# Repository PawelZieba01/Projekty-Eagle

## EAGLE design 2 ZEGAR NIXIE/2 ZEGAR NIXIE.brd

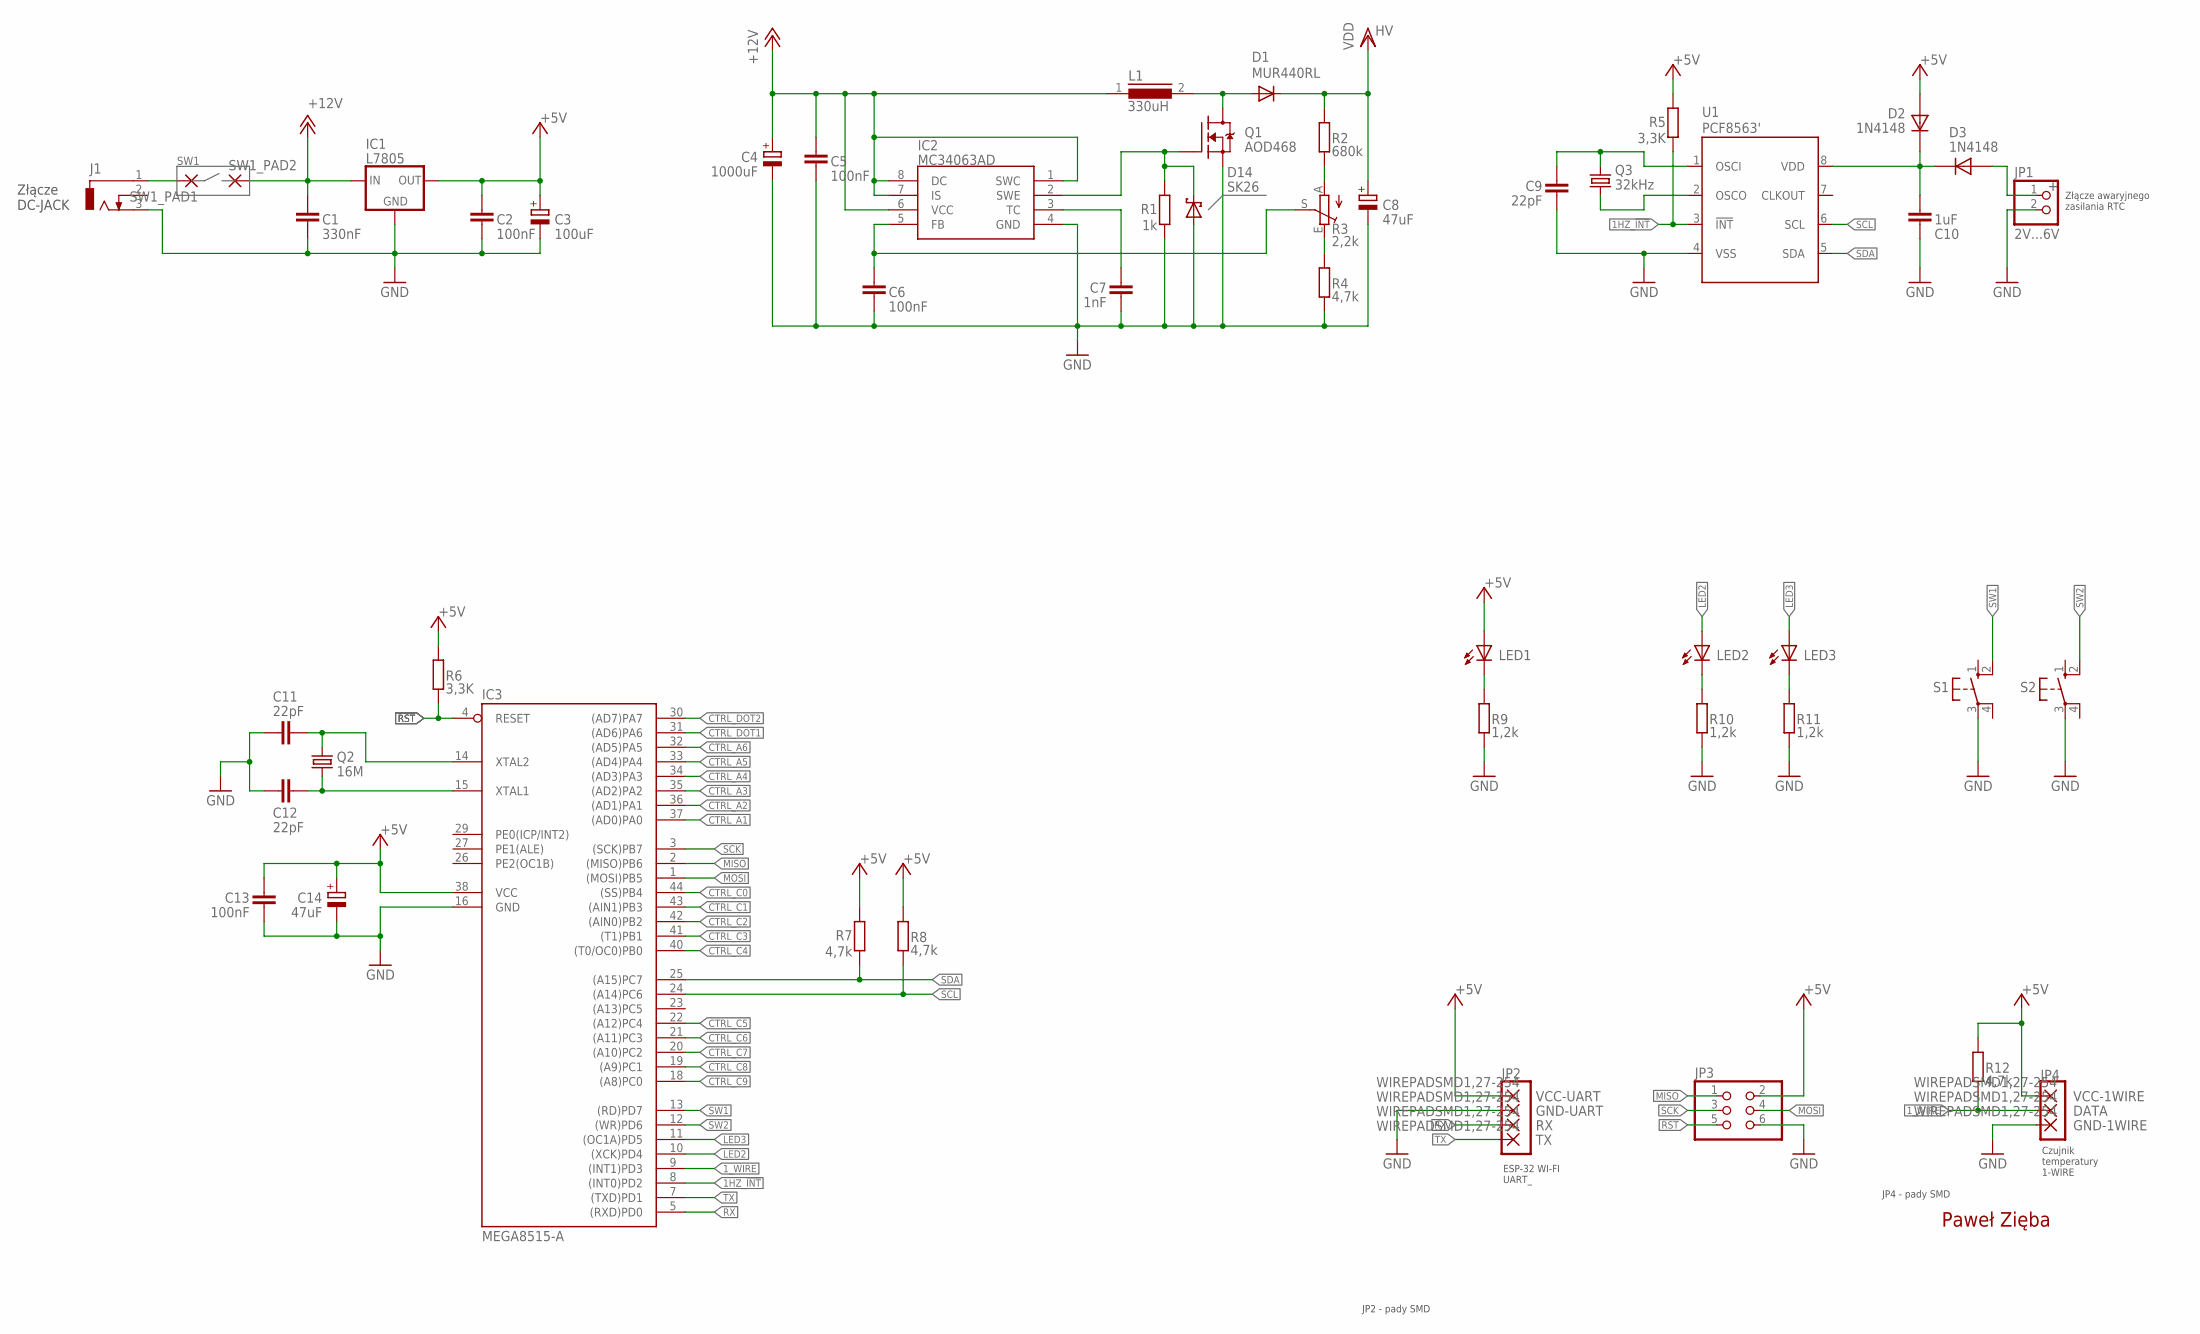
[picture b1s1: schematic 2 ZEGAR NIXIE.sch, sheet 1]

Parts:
C1: 330nF; C1206
C2, C5, C6, C13: 100nF; C1206
C3: 100uF; E5-10,5
C4: 1000uF; E5-10,5
C7: 1nF; C1206
C8: 47uF; E5-13
C9, C11, C12: 22pF; C1206
C10: 1uF; C1206
C14: 47uF; UD-6,3X5,8_NICHICON
D1: MUR440RL; C2673
D2, D3: 1N4148; D1206
D14: SK26; SMB
DATA: WIREPADSMD1,27-254; SMD1,27-2,54
GND-1WIRE: WIREPADSMD1,27-254; SMD1,27-2,54
GND-UART: WIREPADSMD1,27-254; SMD1,27-2,54
IC1: L7805; DPAK
IC2: MC34063AD; SOIC8
IC3: MEGA8515-A; TQFP44
J1: DCJ0303
JP1: 2V...6V; 1X02
JP3: PINHD-2X3; 2X03
L1: 330uH; SFT830D
LED1, LED2, LED3: LED_E; LED_1206
Q1: AOD468; DPAK-TO252
Q2: 16M; 2.5X2.0_KX-6
Q3: 32kHz; TC26H
R1: 1k; R0805
R2: 680k; R0805
R3: 2,2k; CA6V
R4: 4,7k; R0805
R5, R6: 3,3K; R1206
R7, R8, R12: 4,7k; R1206
R9, R10, R11: 1,2k; R1206
RX: WIREPADSMD1,27-254; SMD1,27-2,54
S1, S2: 10-XX; B3F-10XX
SW1_PAD1, SW1_PAD2: 3,81/1,4
TX: WIREPADSMD1,27-254; SMD1,27-2,54
U1: PCF8563'; SO08-IRF
VCC-1WIRE: WIREPADSMD1,27-254; SMD1,27-2,54
VCC-UART: WIREPADSMD1,27-254; SMD1,27-2,54

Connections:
1HZ_!INT: IC3.8 ((INT0)PD2), R5.1, U1.3 (!INT)
1_WIRE: DATA.1, IC3.9 ((INT1)PD3), R12.1
!RST: IC3.4 (RESET), JP3.5, R6.1
+5V: C2.1, C3.+, C13.2, C14.+, D2.1 (+), IC1.3 (OUT), IC3.38 (VCC), JP3.2, LED1.A, R5.2, R6.2, R7.2, R8.2, R12.2, VCC-1WIRE.1, VCC-UART.1
+12V: C1.1, C4.+, C5.1, IC1.1 (IN), IC2.1 (SWC), IC2.6 (VCC), IC2.7 (IS), IC2.8 (DC), L1.1, SW1_PAD2.1
CTRL_A1: IC3.37 ((AD0)PA0); also elsewhere on the board
CTRL_A2: IC3.36 ((AD1)PA1); also elsewhere on the board
CTRL_A3: IC3.35 ((AD2)PA2); also elsewhere on the board
CTRL_A4: IC3.34 ((AD3)PA3); also elsewhere on the board
CTRL_A5: IC3.33 ((AD4)PA4); also elsewhere on the board
CTRL_A6: IC3.32 ((AD5)PA5); also elsewhere on the board
CTRL_C0: IC3.44 ((SS)PB4); also elsewhere on the board
CTRL_C1: IC3.43 ((AIN1)PB3); also elsewhere on the board
CTRL_C2: IC3.42 ((AIN0)PB2); also elsewhere on the board
CTRL_C3: IC3.41 ((T1)PB1); also elsewhere on the board
CTRL_C4: IC3.40 ((T0/OC0)PB0); also elsewhere on the board
CTRL_C5: IC3.22 ((A12)PC4); also elsewhere on the board
CTRL_C6: IC3.21 ((A11)PC3); also elsewhere on the board
CTRL_C7: IC3.20 ((A10)PC2); also elsewhere on the board
CTRL_C8: IC3.19 ((A9)PC1); also elsewhere on the board
CTRL_C9: IC3.18 ((A8)PC0); also elsewhere on the board
CTRL_DOT1: IC3.31 ((AD6)PA6); also elsewhere on the board
CTRL_DOT2: IC3.30 ((AD7)PA7); also elsewhere on the board
GND: C1.2, C2.2, C3.-, C4.-, C5.2, C6.2, C7.2, C8.-, C9.2, C10.2, C11.1, C12.1, C13.1, C14.-, D14.A, GND-1WIRE.1, GND-UART.1, IC1.2 (GND), IC2.4 (GND), IC3.16 (GND), J1.3, JP1.2, JP3.6, Q1.3 (S), R1.1, R4.1, R9.1, R10.1, R11.1, S1.3, S2.3, U1.4 (VSS); also elsewhere on the board
HV: C8.+, D1.C, R2.2; also elsewhere on the board
LED2: IC3.10 ((XCK)PD4), LED2.A
LED3: IC3.11 ((OC1A)PD5), LED3.A
MISO: IC3.2 ((MISO)PB6), JP3.1
MOSI: IC3.1 ((MOSI)PB5), JP3.4
unnamed: J1.1, SW1_PAD1.1
unnamed: R2.1, R3.A
unnamed: C7.1, IC2.3 (TC)
unnamed: R3.E, R4.2
unnamed: C11.2, IC3.14 (XTAL2), Q2.3 (2)
unnamed: D14.C, IC2.2 (SWE), Q1.1 (G), R1.2
unnamed: D1.A, L1.2, Q1.2 (D)
unnamed: C6.1, IC2.5 (FB), R3.S
unnamed: LED1.C, R9.2
unnamed: C12.2, IC3.15 (XTAL1), Q2.1
unnamed: Q3.1, U1.2 (OSCO)
unnamed: C9.1, Q3.2, U1.1 (OSCI)
unnamed: C10.1, D2.2 (-), D3.2 (-), U1.8 (VDD)
unnamed: D3.1 (+), JP1.1
unnamed: LED2.C, R10.2
unnamed: LED3.C, R11.2
RX: IC3.5 ((RXD)PD0), RX.1
SCK: IC3.3 ((SCK)PB7), JP3.3
SCL: IC3.24 ((A14)PC6), R8.1, U1.6 (SCL)
SDA: IC3.25 ((A15)PC7), R7.1, U1.5 (SDA)
SW1: IC3.13 ((RD)PD7), S1.2 (S1)
SW2: IC3.12 ((WR)PD6), S2.2 (S1)
TX: IC3.7 ((TXD)PD1), TX.1

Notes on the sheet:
SW1
Złącze awaryjnego zasilania RTC
Czujnik temperatury 1-WIRE
ESP-32 WI-FI UART_
Paweł Zięba
Złącze DC-JACK
JP2
JP4
JP2 - pady SMD
JP4 - pady SMD

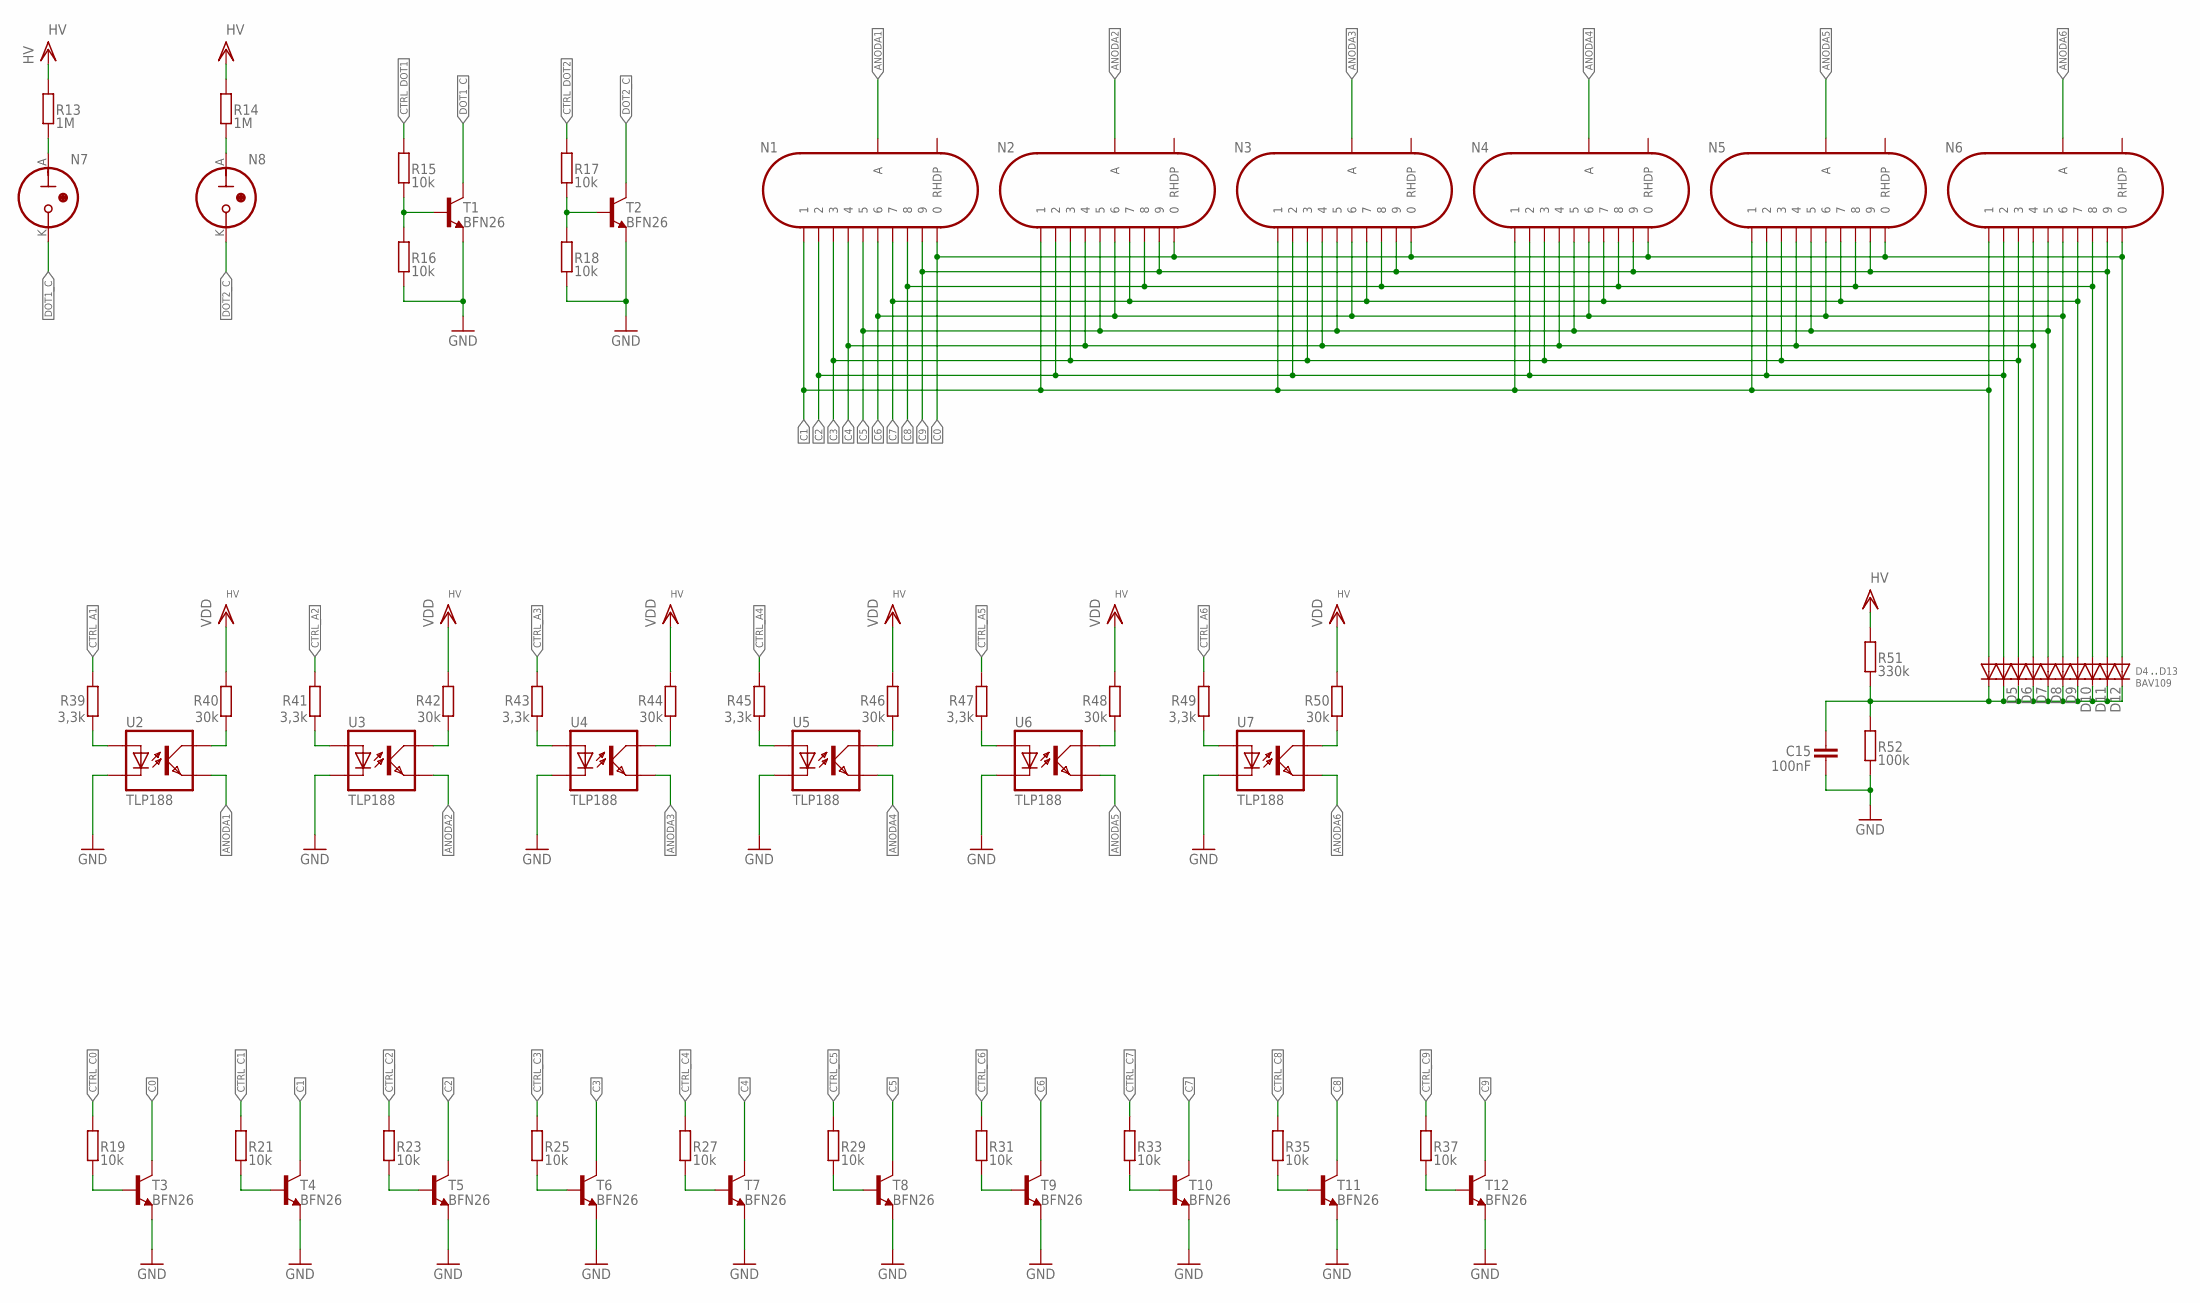
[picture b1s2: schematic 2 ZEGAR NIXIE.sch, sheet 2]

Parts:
C15: 100nF; C1206
D4, D5, D6, D7, D8, D9, D10, D11, D12: DIODE-MINIMELF; MINIMELF
D13: BAV109; MINIMELF
N1, N2, N3, N4, N5, N6: IN-8-2
N7, N8: IN-3
R13, R14: 1M; R1206
R15, R16, R17, R18, R19, R21, R23, R25, R27, R29, R31, R33, R35, R37: 10k; R0805
R39, R41, R43, R45, R47, R49: 3,3k; R0805
R40, R42, R44, R46, R48, R50: 30k; R1206
R51: 330k; R1206
R52: 100k; R1206
T1, T2, T3, T4, T5, T6, T7, T8, T9, T10, T11, T12: BFN26; SOT23-BEC
U2, U3, U4, U5, U6, U7: TLP188; 11-4M1S

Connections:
ANODA1: N1.A, U2.P$4 (EMIT)
ANODA2: N2.A, U3.P$4 (EMIT)
ANODA3: N3.A, U4.P$4 (EMIT)
ANODA4: N4.A, U5.P$4 (EMIT)
ANODA5: N5.A, U6.P$4 (EMIT)
ANODA6: N6.A, U7.P$4 (EMIT)
C0: D13.A, N1.0, N2.0, N3.0, N4.0, N5.0, N6.0, T3.C
C1: D4.A, N1.1, N2.1, N3.1, N4.1, N5.1, N6.1, T4.C
C2: D5.A, N1.2, N2.2, N3.2, N4.2, N5.2, N6.2, T5.C
C3: D6.A, N1.3, N2.3, N3.3, N4.3, N5.3, N6.3, T6.C
C4: D7.A, N1.4, N2.4, N3.4, N4.4, N5.4, N6.4, T7.C
C5: D8.A, N1.5, N2.5, N3.5, N4.5, N5.5, N6.5, T8.C
C6: D9.A, N1.6, N2.6, N3.6, N4.6, N5.6, N6.6, T9.C
C7: D10.A, N1.7, N2.7, N3.7, N4.7, N5.7, N6.7, T10.C
C8: D11.A, N1.8, N2.8, N3.8, N4.8, N5.8, N6.8, T11.C
C9: D12.A, N1.9, N2.9, N3.9, N4.9, N5.9, N6.9, T12.C
CTRL_A1: R39.1; also elsewhere on the board
CTRL_A2: R41.1; also elsewhere on the board
CTRL_A3: R43.1; also elsewhere on the board
CTRL_A4: R45.1; also elsewhere on the board
CTRL_A5: R47.1; also elsewhere on the board
CTRL_A6: R49.1; also elsewhere on the board
CTRL_C0: R19.2; also elsewhere on the board
CTRL_C1: R21.2; also elsewhere on the board
CTRL_C2: R23.2; also elsewhere on the board
CTRL_C3: R25.2; also elsewhere on the board
CTRL_C4: R27.2; also elsewhere on the board
CTRL_C5: R29.2; also elsewhere on the board
CTRL_C6: R31.2; also elsewhere on the board
CTRL_C7: R33.2; also elsewhere on the board
CTRL_C8: R35.2; also elsewhere on the board
CTRL_C9: R37.2; also elsewhere on the board
CTRL_DOT1: R15.2; also elsewhere on the board
CTRL_DOT2: R17.2; also elsewhere on the board
DOT1_C: N7.K, T1.C
DOT2_C: N8.K, T2.C
GND: C15.2, R16.1, R18.1, R52.1, T1.E, T2.E, T3.E, T4.E, T5.E, T6.E, T7.E, T8.E, T9.E, T10.E, T11.E, T12.E, U2.P$3 (C), U3.P$3 (C), U4.P$3 (C), U5.P$3 (C), U6.P$3 (C), U7.P$3 (C); also elsewhere on the board
HV: R13.2, R14.2, R40.2, R42.2, R44.2, R46.2, R48.2, R50.2, R51.2; also elsewhere on the board
unnamed: C15.1, D4.C, D5.C, D6.C, D7.C, D8.C, D9.C, D10.C, D11.C, D12.C, D13.C, R51.1, R52.2
unnamed: N7.A, R13.1
unnamed: N8.A, R14.1
unnamed: R15.1, R16.2, T1.B
unnamed: R17.1, R18.2, T2.B
unnamed: R40.1, U2.P$6 (COL)
unnamed: R42.1, U3.P$6 (COL)
unnamed: R44.1, U4.P$6 (COL)
unnamed: R46.1, U5.P$6 (COL)
unnamed: R48.1, U6.P$6 (COL)
unnamed: R50.1, U7.P$6 (COL)
unnamed: R39.2, U2.P$1 (A)
unnamed: R41.2, U3.P$1 (A)
unnamed: R43.2, U4.P$1 (A)
unnamed: R49.2, U7.P$1 (A)
unnamed: R47.2, U6.P$1 (A)
unnamed: R45.2, U5.P$1 (A)
unnamed: R19.1, T3.B
unnamed: R21.1, T4.B
unnamed: R23.1, T5.B
unnamed: R25.1, T6.B
unnamed: R27.1, T7.B
unnamed: R29.1, T8.B
unnamed: R31.1, T9.B
unnamed: R33.1, T10.B
unnamed: R35.1, T11.B
unnamed: R37.1, T12.B

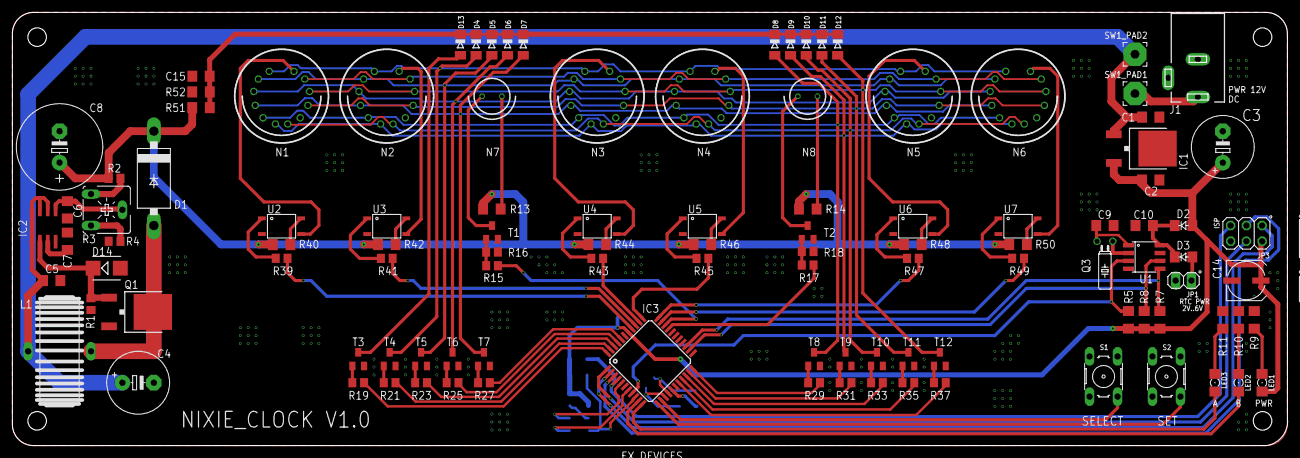
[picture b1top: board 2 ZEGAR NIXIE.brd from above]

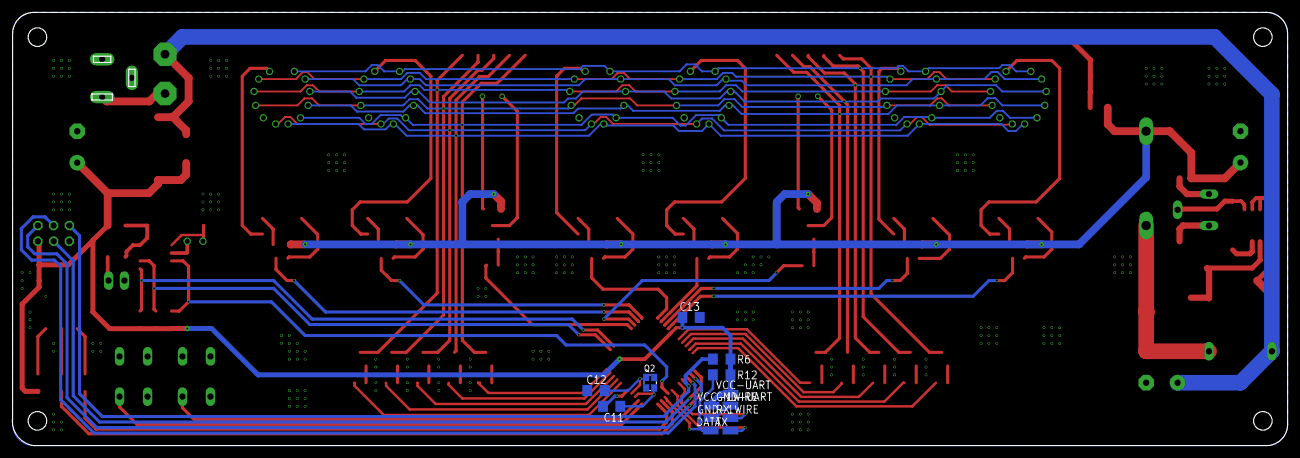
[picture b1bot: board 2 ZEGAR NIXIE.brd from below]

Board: 2 copper layers, 206.1 x 70.0 mm, 122 parts (13 on the bottom side), 97 nets.

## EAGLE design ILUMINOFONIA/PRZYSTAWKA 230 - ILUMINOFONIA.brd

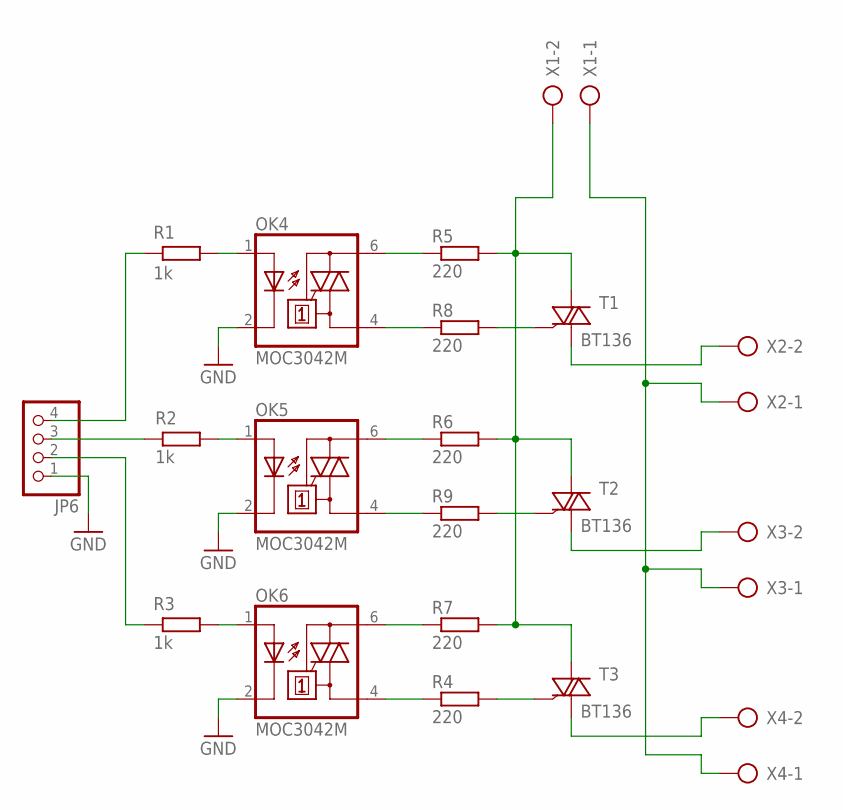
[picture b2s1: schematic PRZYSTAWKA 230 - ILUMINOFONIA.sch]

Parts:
JP6: PINHD-1X4; 1X04
OK4, OK5, OK6: MOC3042M; DIL06
R1, R2, R3: 1k; 204/5
R4, R5, R6, R7, R8, R9: 220; 204/5
T1, T2, T3: BT136; TO220AB
X1, X2, X3, X4: AK300/2

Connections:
GND: JP6.1, OK4.2 (C), OK5.2 (C), OK6.2 (C)
unnamed: OK5.1 (A), R2.P$2 (2)
unnamed: OK4.1 (A), R1.P$2 (2)
unnamed: OK6.1 (A), R3.P$2 (2)
unnamed: OK4.6 (A2), R5.P$1 (1)
unnamed: OK4.4 (A1), R8.P$1 (1)
unnamed: JP6.4, R1.P$1 (1)
unnamed: JP6.3, R2.P$1 (1)
unnamed: JP6.2, R3.P$1 (1)
unnamed: OK5.6 (A2), R6.P$1 (1)
unnamed: OK5.4 (A1), R9.P$1 (1)
unnamed: OK6.6 (A2), R7.P$1 (1)
unnamed: OK6.4 (A1), R4.P$1 (1)
unnamed: R4.P$2 (2), T3.3 (G)
unnamed: R9.P$2 (2), T2.3 (G)
unnamed: R8.P$2 (2), T1.3 (G)
unnamed: R5.P$2 (2), R6.P$2 (2), R7.P$2 (2), T1.2 (A2), T2.2 (A2), T3.2 (A2), X1.2
unnamed: T3.1 (A1), X4.2
unnamed: T2.1 (A1), X3.2
unnamed: T1.1 (A1), X2.2
unnamed: X1.1, X2.1, X3.1, X4.1

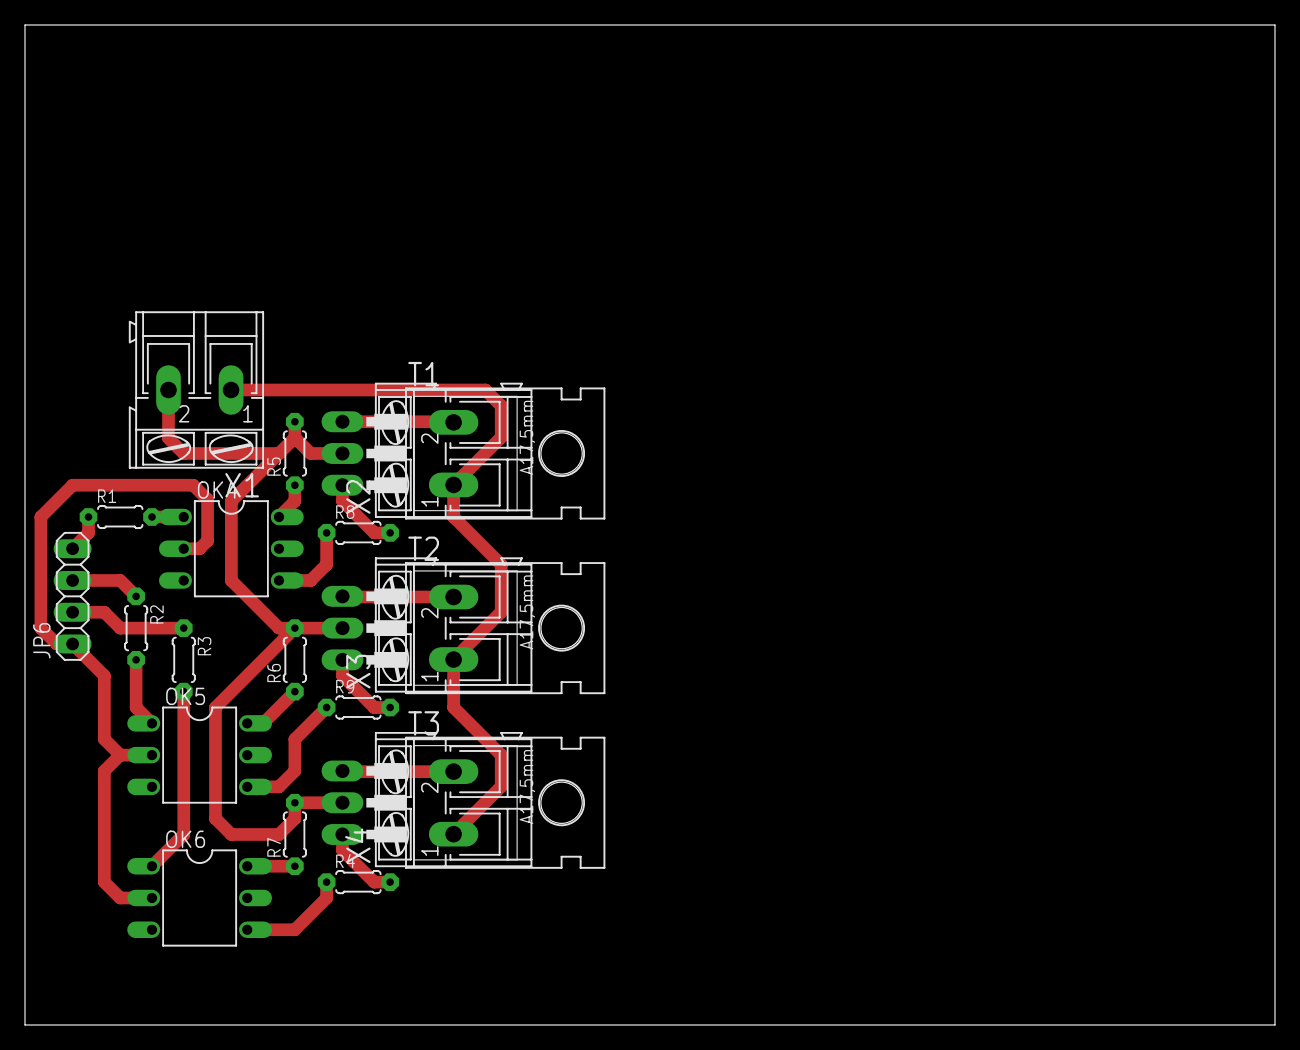
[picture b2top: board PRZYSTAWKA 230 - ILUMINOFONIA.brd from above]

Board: 2 copper layers, 100.0 x 80.0 mm, 20 parts (0 on the bottom side), 21 nets.

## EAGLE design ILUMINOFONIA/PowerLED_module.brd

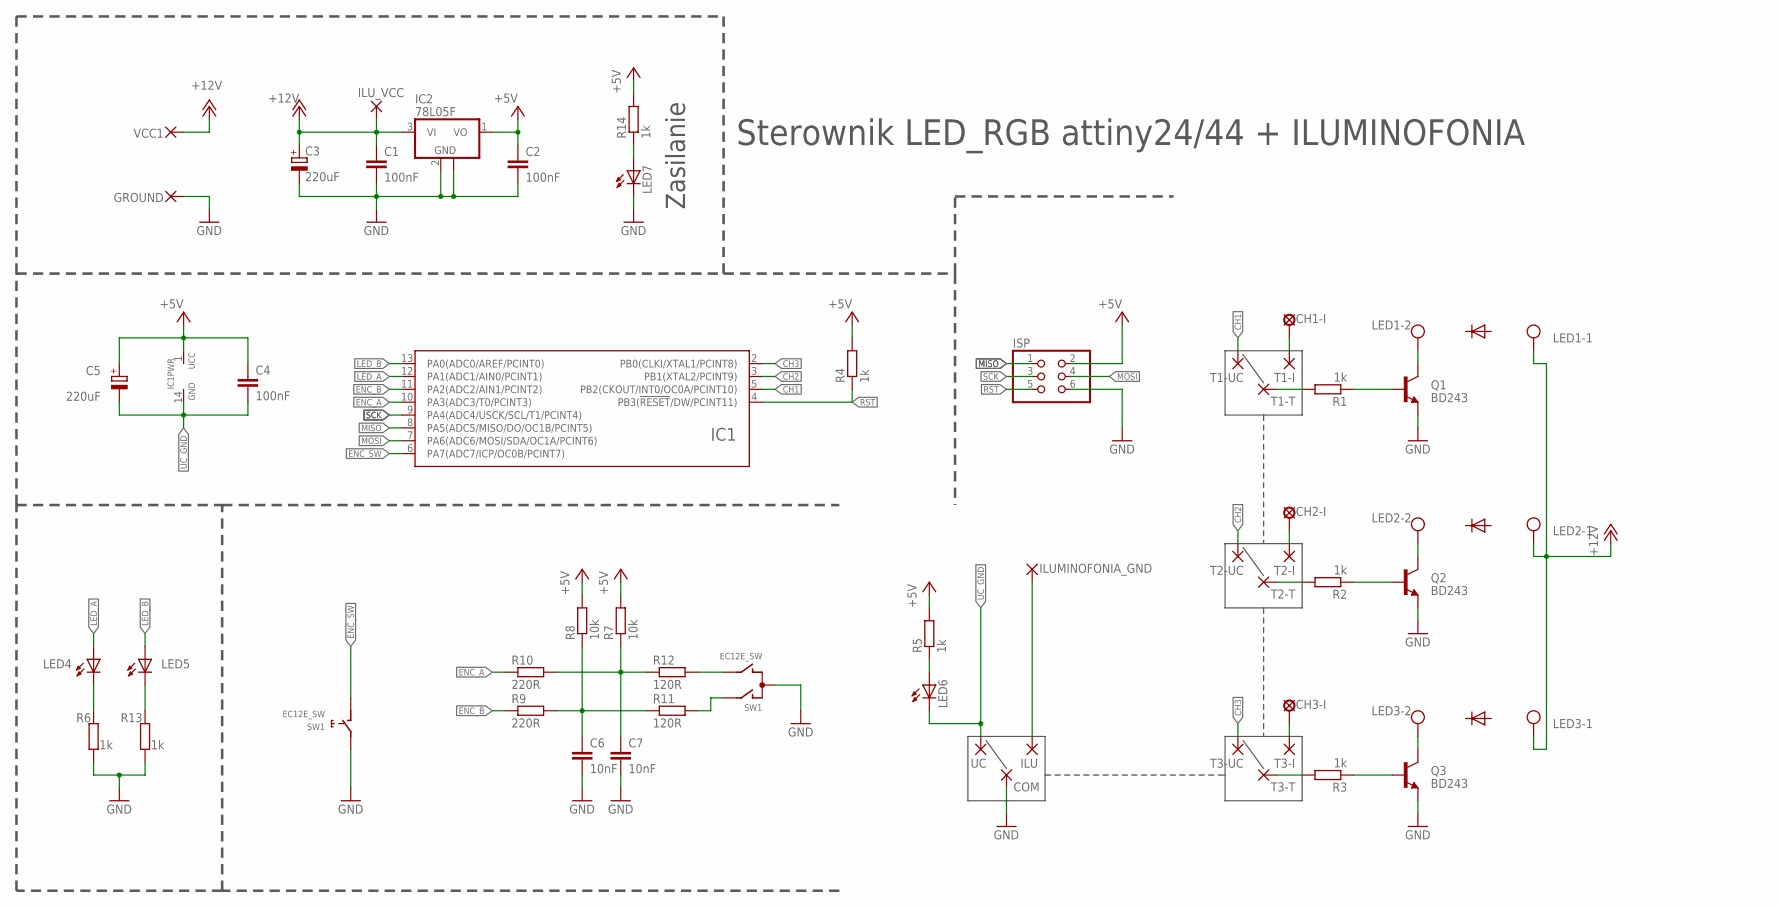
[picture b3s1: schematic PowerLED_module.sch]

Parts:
C1, C2, C4: 100nF; C50-45-75
C3, C5: 220uF; E2,5-6
C6, C7: 10nF; C50-45-75
CH1-I, CH2-I, CH3-I: SE14
COM: 1,6/0,9
GROUND: 3,81/1,4
IC1: ATTINY24/44/84-SSU; SOIC14
IC2: 78L05F; SOT89
ILU: 1,6/0,9
ILUMINOFONIA_GND: 3,81/1,4
ILU_VCC: 3,81/1,4
ISP: PINHD-2X3; 2X03
LED1, LED2, LED3: AK300/2
LED4, LED5, LED6, LED7: LED5MM
Q1, Q2, Q3: BD243; TO220
R1, R2, R3, R5, R6, R13, R14: 1k; 204/7
R4: 1k; M1206
R7, R8: 10k; M1206
R9, R10: 220R; M1206
R11, R12: 120R; M1206
SW1: EC12E_SW; ALPS_EC12E_SW
T1-I, T1-T, T1-UC, T2-I, T2-T, T2-UC, T3-I, T3-T, T3-UC: 1,6/0,9
UC: 1,6/0,9
VCC1: 3,81/1,4

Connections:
+5V: C2.P$1 (1), C4.P$1 (1), C5.P$1 (+), IC1.1 (UCC), IC2.1 (VO), ISP.2, R4.2, R5.P$2 (2), R7.2, R8.2, R14.P$2 (2)
+12V: C1.P$1 (1), C3.P$1 (+), IC2.3 (VI), ILU_VCC.1, LED1.1, LED2.1, LED3.1, VCC1.1
CH1: IC1.5 (PB2(CKOUT/INT0/OC0A/PCINT10)), T1-UC.1
CH2: IC1.3 (PB1(XTAL2/PCINT9)), T2-UC.1
CH3: IC1.2 (PB0(CLKI/XTAL1/PCINT8)), T3-UC.1
ENC_A: IC1.10 (PA3(ADC3/T0/PCINT3)), R10.1
ENC_B: IC1.11 (PA2(ADC2/AIN1/PCINT2)), R9.1
ENC_SW: IC1.6 (PA7(ADC7/ICP/OC0B/PCINT7)), SW1.D (1)
GND: C1.P$2 (2), C2.P$2 (2), C3.P$2 (-), C6.P$2 (2), C7.P$2 (2), COM.1, GROUND.1, IC2.2 (GND), IC2.2@1 (GND), ISP.6, LED7.K (C), Q1.3 (E), Q2.3 (E), Q3.3 (E), R6.P$1 (1), R13.P$1 (1), SW1.C, SW1.E (2)
ILU_GND: ILU.1, ILUMINOFONIA_GND.1
LED_A: IC1.12 (PA1(ADC1/AIN0/PCINT1)), LED4.A
LED_B: IC1.13 (PA0(ADC0/AREF/PCINT0)), LED5.A
MISO: IC1.8 (PA5(ADC5/MISO/DO/OC1B/PCINT5)), ISP.1
MOSI: IC1.7 (PA6(ADC6/MOSI/SDA/OC1A/PCINT6)), ISP.4
unnamed: LED1.2, Q1.2 (C)
unnamed: LED3.2, Q3.2 (C)
unnamed: LED2.2, Q2.2 (C)
unnamed: Q3.1 (B), R3.P$1 (1)
unnamed: R3.P$2 (2), T3-T.1
unnamed: Q2.1 (B), R2.P$1 (1)
unnamed: R1.P$2 (2), T1-T.1
unnamed: Q1.1 (B), R1.P$1 (1)
unnamed: R2.P$2 (2), T2-T.1
unnamed: CH1-I.MP, T1-I.1
unnamed: CH2-I.MP, T2-I.1
unnamed: CH3-I.MP, T3-I.1
unnamed: C7.P$1 (1), R7.1, R10.2, R12.1
unnamed: R12.2, SW1.B
unnamed: R11.2, SW1.A
unnamed: C6.P$1 (1), R8.1, R9.2, R11.1
unnamed: LED4.K (C), R6.P$2 (2)
unnamed: LED5.K (C), R13.P$2 (2)
unnamed: LED6.A, R5.P$1 (1)
unnamed: LED7.A, R14.P$1 (1)
RST: IC1.4 (PB3(!RESET!/DW/PCINT11)), ISP.5, R4.1
SCK: IC1.9 (PA4(ADC4/USCK/SCL/T1/PCINT4)), ISP.3
UC_GND: C4.P$2 (2), C5.P$2 (-), IC1.14 (GND), LED6.K (C), UC.1

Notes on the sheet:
Sterownik LED_RGB attiny24/44 + ILUMINOFONIA
Zasilanie

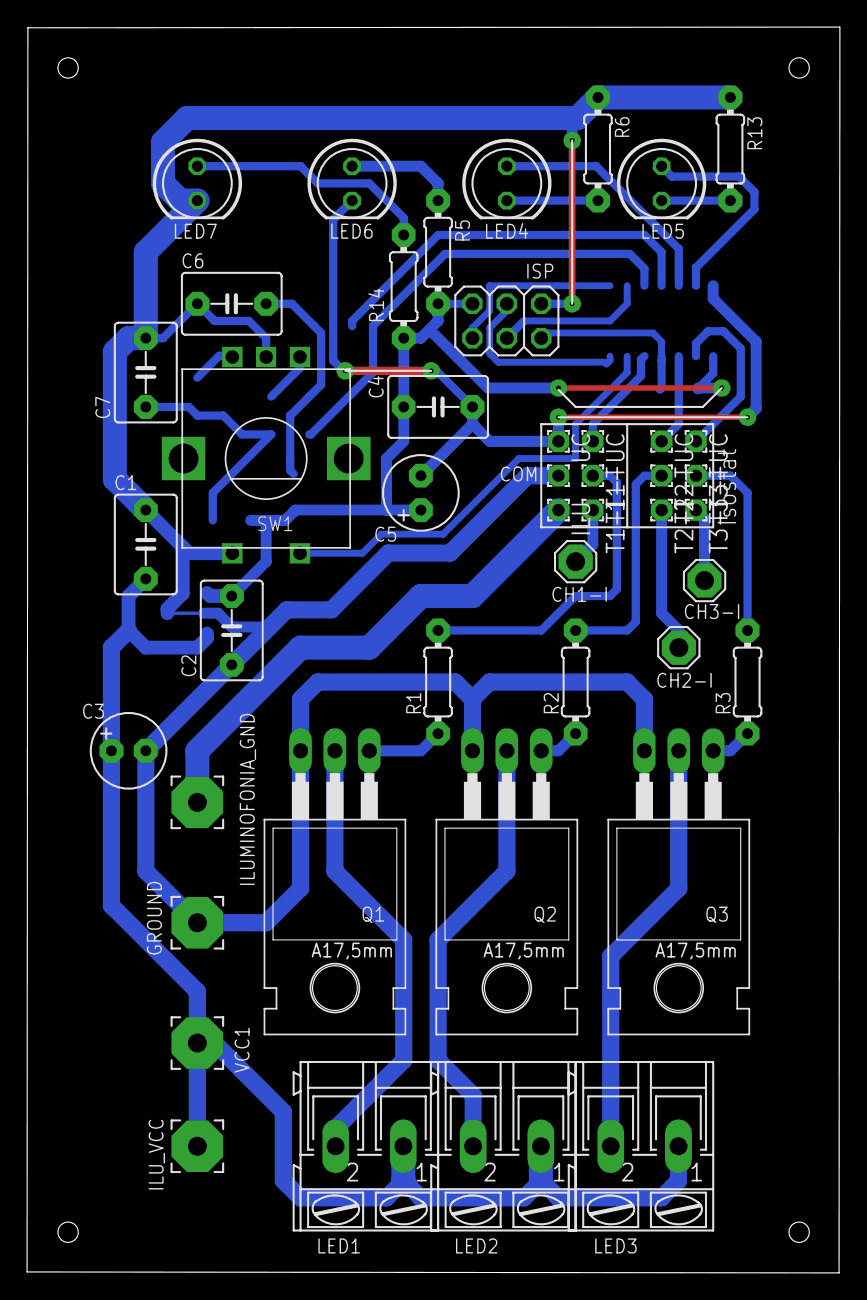
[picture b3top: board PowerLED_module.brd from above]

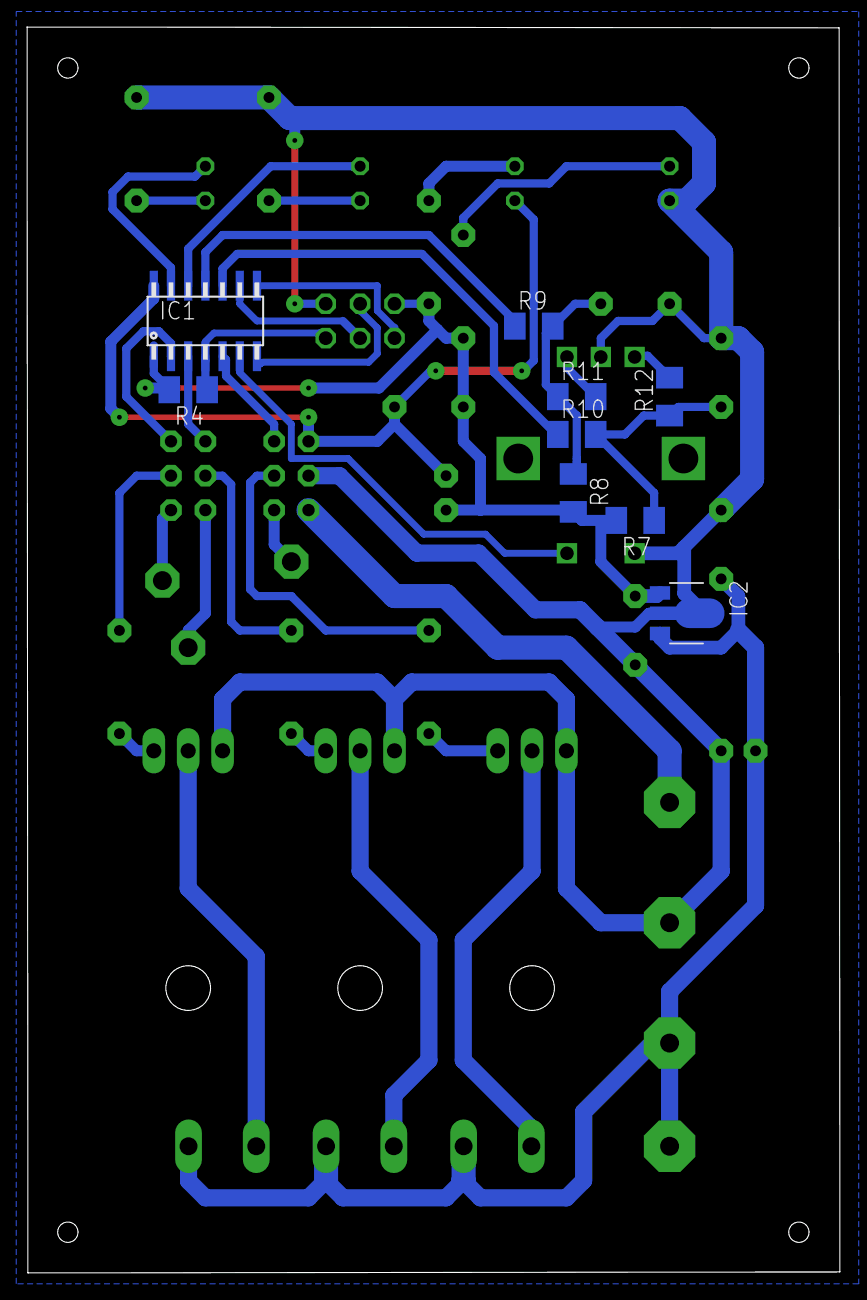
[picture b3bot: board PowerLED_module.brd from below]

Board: 2 copper layers, 60.0 x 92.0 mm, 54 parts (9 on the bottom side), 37 nets.

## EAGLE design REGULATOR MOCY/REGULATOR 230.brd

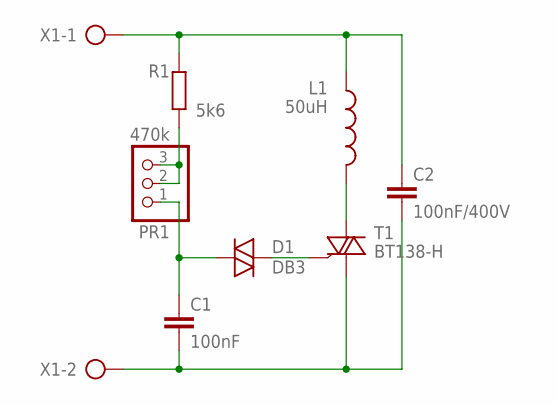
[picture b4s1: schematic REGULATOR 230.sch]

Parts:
C1: 100nF; 150-72-183
C2: 100nF/400V; 150-72-183
D1: DB3; DO-35-PION(3MM)
L1: 50uH; C5-15
PR1: 470k; 1X03
R1: 5k6; 204/7
T1: BT138-H; TO220BH
X1: AK300/2

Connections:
unnamed: C2.P$1 (1), L1.P$1 (1), R1.P$2 (2), X1.1
unnamed: PR1.2, PR1.3, R1.P$1 (1)
unnamed: C1.P$1 (1), D1.P$1 (1), PR1.1
unnamed: D1.P$2 (2), T1.G
unnamed: L1.P$2 (2), T1.T2 (A2)
unnamed: C1.P$2 (2), C2.P$2 (2), T1.T1 (A1), X1.2

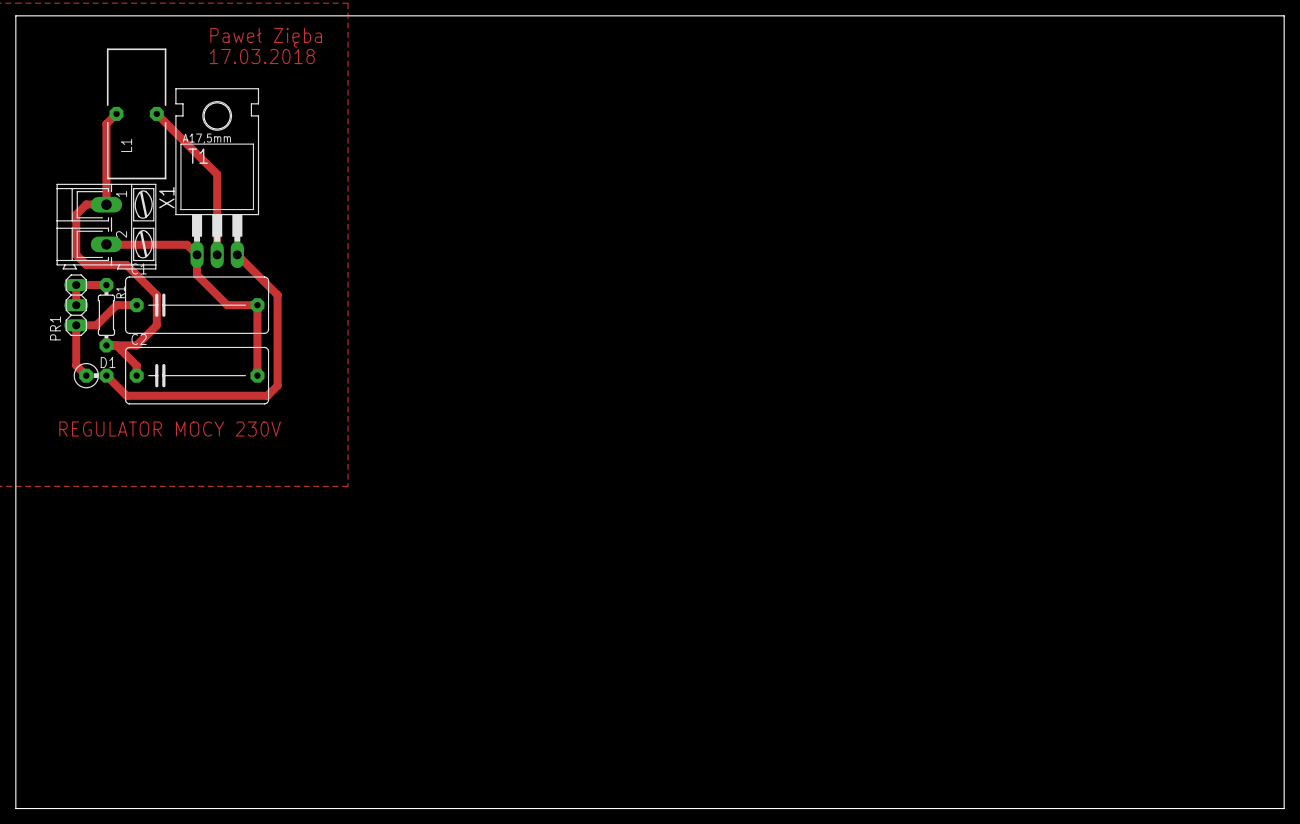
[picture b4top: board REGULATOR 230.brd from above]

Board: 2 copper layers, 160.0 x 100.0 mm, 8 parts (0 on the bottom side), 6 nets.

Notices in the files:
parts and their libraries:
crystal-geyer_V1_0: Copyright: Geyer-Electronic
